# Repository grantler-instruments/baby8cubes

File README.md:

# baby8cubes
## Description
baby8cubes is hardware 8 step sequencer with visual, audio and midi output. Each step can be controlled by placing and rotating a cube.

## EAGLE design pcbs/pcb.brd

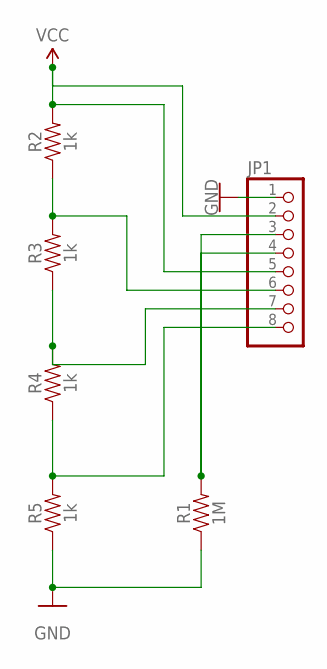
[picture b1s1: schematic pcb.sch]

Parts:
JP1: PINHD-1X8-3.5MM; 1X08-3.5MM
R1: 1M; AXIAL-0.3
R2, R3, R4, R5: 1k; AXIAL-0.3

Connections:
GND: JP1.1, R1.P$1 (1), R5.P$1 (1)
unnamed: JP1.8, R4.P$1 (1), R5.P$2 (2)
unnamed: JP1.7, R3.P$1 (1), R4.P$2 (2)
unnamed: JP1.6, R2.P$1 (1), R3.P$2 (2)
unnamed: JP1.3, JP1.4, R1.P$2 (2)
VCC: JP1.2, JP1.5, R2.P$2 (2)

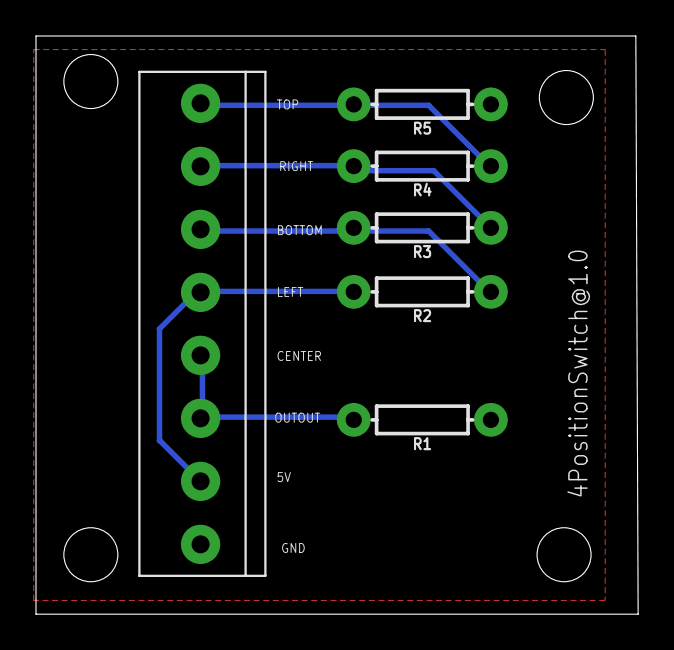
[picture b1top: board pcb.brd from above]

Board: 2 copper layers, 33.5 x 32.1 mm, 6 parts (0 on the bottom side), 6 nets.

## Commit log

2019-05-30 now tested with teensy and neopixels
2019-06-02 added pcb designs
2023-08-25 updated firmware (wip)
2023-08-25 fixed pin mapping, implemented play and bpm
2024-11-01 added tof for velocity controls
2024-11-01 added motion sensor for speed modulation
2024-11-07 mapping distance to velocity
2024-11-27 triggering drum samples via midi
2024-11-28 fixed patching
2024-12-03 added filter and bit crusher effects for y axis control
2024-12-03 mapped y rotation to speed modulator
2024-12-04 mapped distance to volume
2024-12-04 wired up main mixer to usb output
2024-12-08 sending midi notes per step
2024-12-26 added cube pcb test firmware
2025-01-15 fixed signal pins for mux
2025-01-15 changed analog input pins
2025-01-17 added mux tester firmware
2025-01-17 trying to cleanup the firmware
2025-01-20 changed mux sig pins and changing led color per step
2025-01-23 added feedback for changed cube
2025-01-23 added seasaw mode
2025-02-25 fixed quick ligh up when placing a cube
2025-02-25 adjusted colors
2025-03-29 added midi clock out, closes #1
2025-04-16 fixed clock
2025-04-17 updated samples, closes #8
2025-04-18 sending noteoff message of last step, closes #10
2025-04-18 removed comments, prepared reset
2025-04-18 refactored neopixel state management, should be easier now to handle cube placed feedback, closes #6
2025-04-22 flattening accleration
2025-04-23 some cleanup and hopefully fixed jumpy distance sensor
2025-04-23 some clocking fixes
2025-05-07 some acceleration fixes
2025-06-10 added missing changed flag on clear
2025-06-10 fixed typo
2025-06-10 setting headphone volume based on hand distance on switch on
2025-06-11 setting volume on setup and adjusted jumpy threshold

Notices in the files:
parts and their libraries:
SparkFun-Resistors: Licensing: Creative Commons ShareAlike 4.0 International - https://creativecommons.org/licenses/by-sa/4.0
